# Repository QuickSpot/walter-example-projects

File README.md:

# Example projects for Walter

This repository contains open-source projects built with the Walter module.
While the example directories in the library projects contain small source-code
snippets, these projects are fully fledged hardware and software implementations
that can be used as a basis for your own work or as a source of inspiration.

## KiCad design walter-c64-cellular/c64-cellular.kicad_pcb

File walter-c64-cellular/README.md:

# Walter based Comodore 64 multi-radio modem

## Introduction
This repository contains the hardware design files of a Walter based expansion card for the
Commodore 64 user port. Walter connects to the user port via UART which allows the C64 to make use 
of the connectivity and compute power of the QuickSpot Walter module.

## The hardware

The hardware is based on the [QuickSpot Walter](https://www.quickspot.io) module which combines 
multiple radio technologies in a single module. This gives the C64 multiradio modem access to Wi-Fi,
BLE, LTE Cat-M1, LTE Cat-NB1/2 and GNSS. The module is powered through it's USB-C connector which is
also used to program it. The connection to the C64 is made through the UART which is available on
the user port. 

As the user port's UART is at 5V TTL level and the Walter module's IO ports work at 3.3V a level
shifter is required. Two bi-directional MOSFET based level shifters are implemented on the board.
The high side is fed with the 5V coming from the C64 user port, the low side is fed with the 3.3V 
coming from the Walter module.

## The software

The basic software is the [Walter modem passthrough example](https://github.com/QuickSpot/walter-arduino/tree/main/examples/passthrough) which exposes the AT command interface from the Sequans GM02SP directly
to the C64.

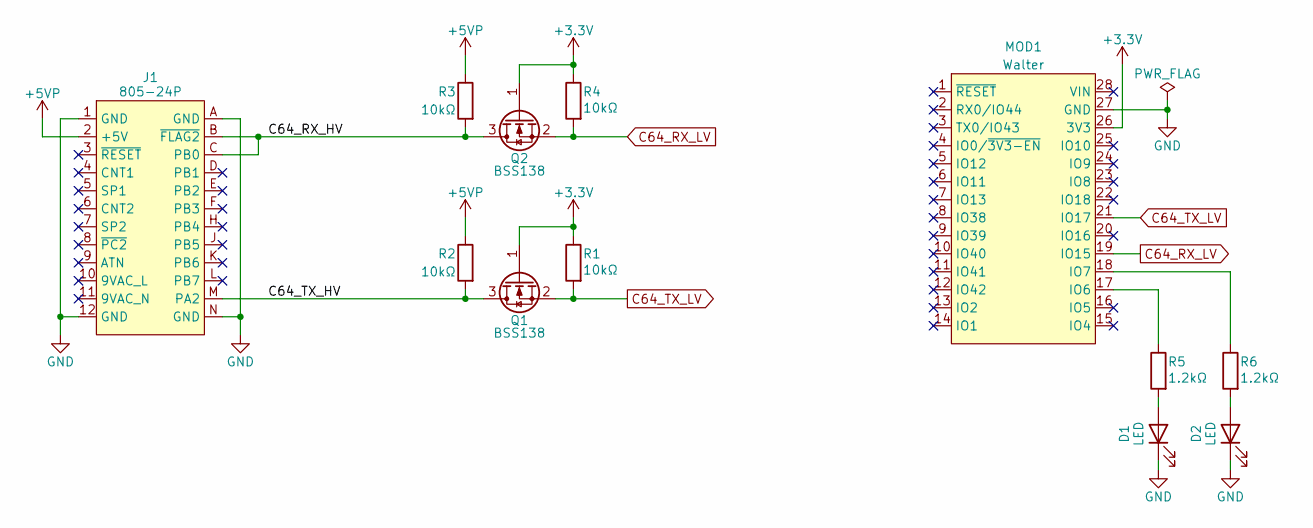
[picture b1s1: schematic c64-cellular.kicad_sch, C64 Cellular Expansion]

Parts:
D1, D2: LED; LED_0603_1608Metric
J1: 805-24P
MOD1: Walter; walter-socket
Q1, Q2: BSS138
R1, R2, R3, R4: 10kΩ; R_0603_1608Metric
R5, R6: 1.2kΩ; R_0603_1608Metric

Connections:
+3.3V: MOD1.26 (3V3), Q1.1 (G), Q2.1 (G), R1.1, R4.1
+5VP: J1.2 (+5V), R2.1, R3.1
/C64_RX_HV: J1.B (~FLAG2), J1.C (PB0), Q2.3 (D), R3.2
/C64_TX_HV: J1.M (PA2), Q1.3 (D), R2.2
C64_RX_LV: MOD1.19 (IO15), Q2.2 (S), R4.2
C64_TX_LV: MOD1.21 (IO17), Q1.2 (S), R1.2
GND: D1.1 (K), D2.1 (K), J1.1 (GND), J1.12 (GND), J1.A (GND), J1.N (GND), MOD1.27 (GND)
unnamed: D1.2 (A), R5.2
unnamed: D2.2 (A), R6.2
unnamed: MOD1.17 (IO6), R5.1
unnamed: MOD1.18 (IO7), R6.1

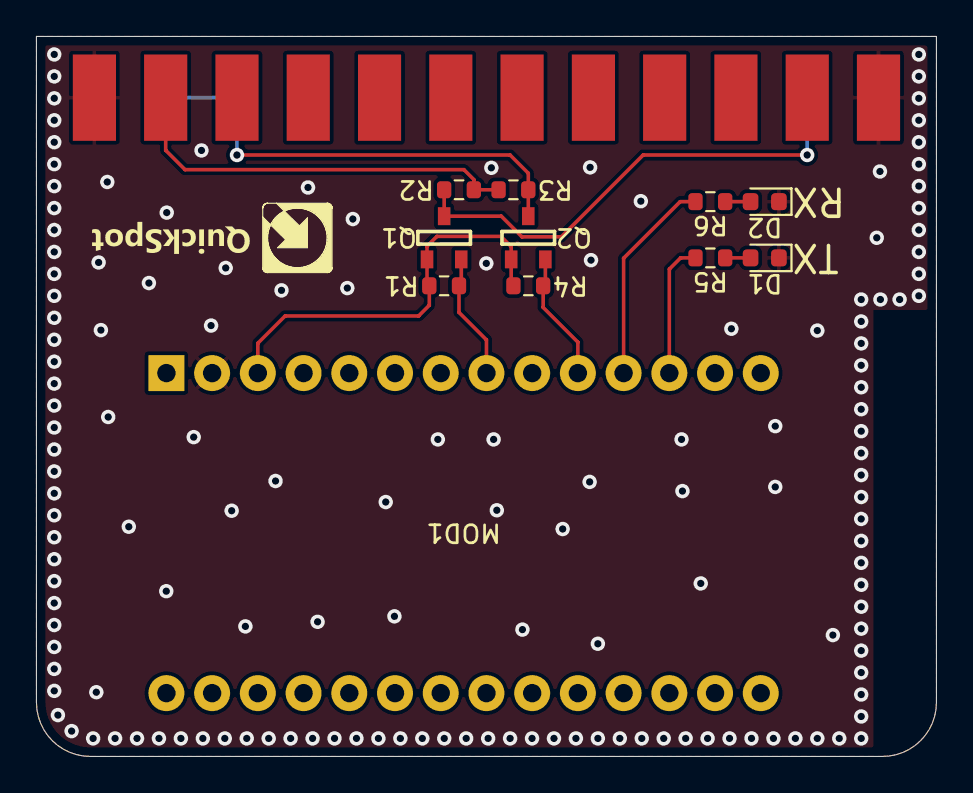
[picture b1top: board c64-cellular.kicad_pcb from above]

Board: 2 copper layers, 50.0 x 40.0 mm, 12 parts (0 on the bottom side), 11 nets.

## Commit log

2026-01-23 Added 64-bit bluecherry client
2026-02-16 Added the Walter Camera project
2026-02-16 Removed mistaken submodule
2026-02-16 Added Walter camera project
2026-04-01 Added walter-audio-streaming example
2026-05-19 Added walter-as-wifi-ap example
